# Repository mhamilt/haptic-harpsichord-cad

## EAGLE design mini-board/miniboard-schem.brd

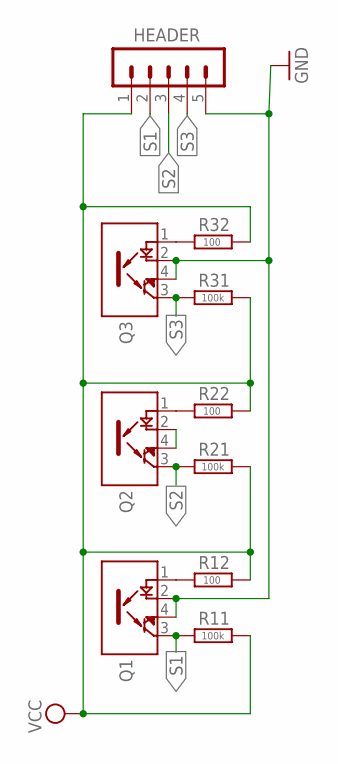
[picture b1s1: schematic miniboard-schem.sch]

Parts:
HEADER: 0; MA05-1
Q1, Q2, Q3: QRE1113; DIP400W50P180L360H200Q4
R11, R21, R31: 100k; 0207/10
R12, R22, R32: 100; 0207/10

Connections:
GND: HEADER.5, Q1.2 (C), Q1.4 (ET), Q3.2 (C), Q3.4 (ET)
unnamed: Q3.1 (A), R32.2
unnamed: Q2.1 (A), R22.2
unnamed: Q2.2 (C), Q2.4 (ET)
unnamed: Q1.1 (A), R12.2
S1: HEADER.2, Q1.3 (CT), R11.2
S2: HEADER.3, Q2.3 (CT), R21.2
S3: HEADER.4, Q3.3 (CT), R31.2
VCC: HEADER.1, R11.1, R12.1, R21.1, R22.1, R31.1, R32.1

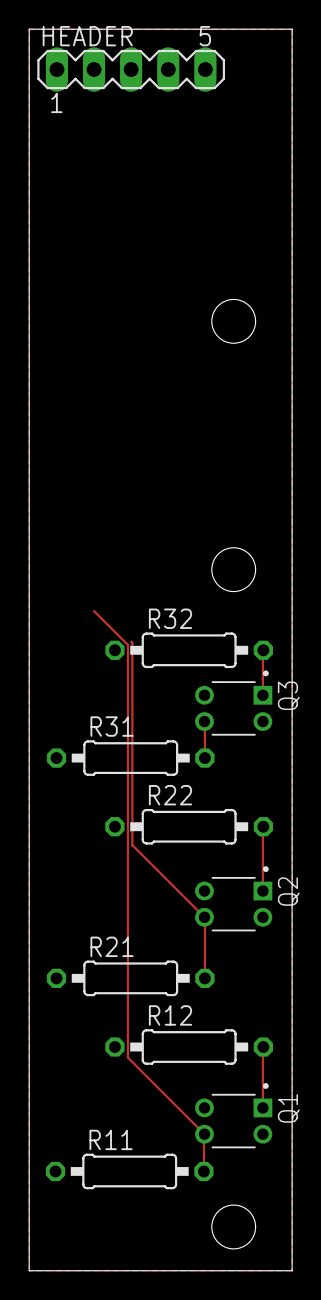
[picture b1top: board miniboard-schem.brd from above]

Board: 2 copper layers, 18.0 x 85.0 mm, 10 parts (0 on the bottom side), 9 nets.
